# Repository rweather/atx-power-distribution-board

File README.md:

ATX Power Distribution Board
============================

This repository contains a design for an adapter board that connects
to a standard 24-pin ATX power supply connector and makes the
voltage rails available for homebrew computer use.

The board is designed to be retrofitted into an ITX computer case,
with the ITX power button, power LED, hdd LED, and reset button
connected to the board to provide power on/off control.

* [Schematic](schematics/ATX-Power-Distribution-Board/PDF/ATX-Power-Distribution-Board.pdf)

## License

Distributed under the terms of the MIT license.

## Contact

For more information on this code, to report bugs, or to suggest
improvements, please contact the author Rhys Weatherley via
[email](mailto:rhys.weatherley@gmail.com).

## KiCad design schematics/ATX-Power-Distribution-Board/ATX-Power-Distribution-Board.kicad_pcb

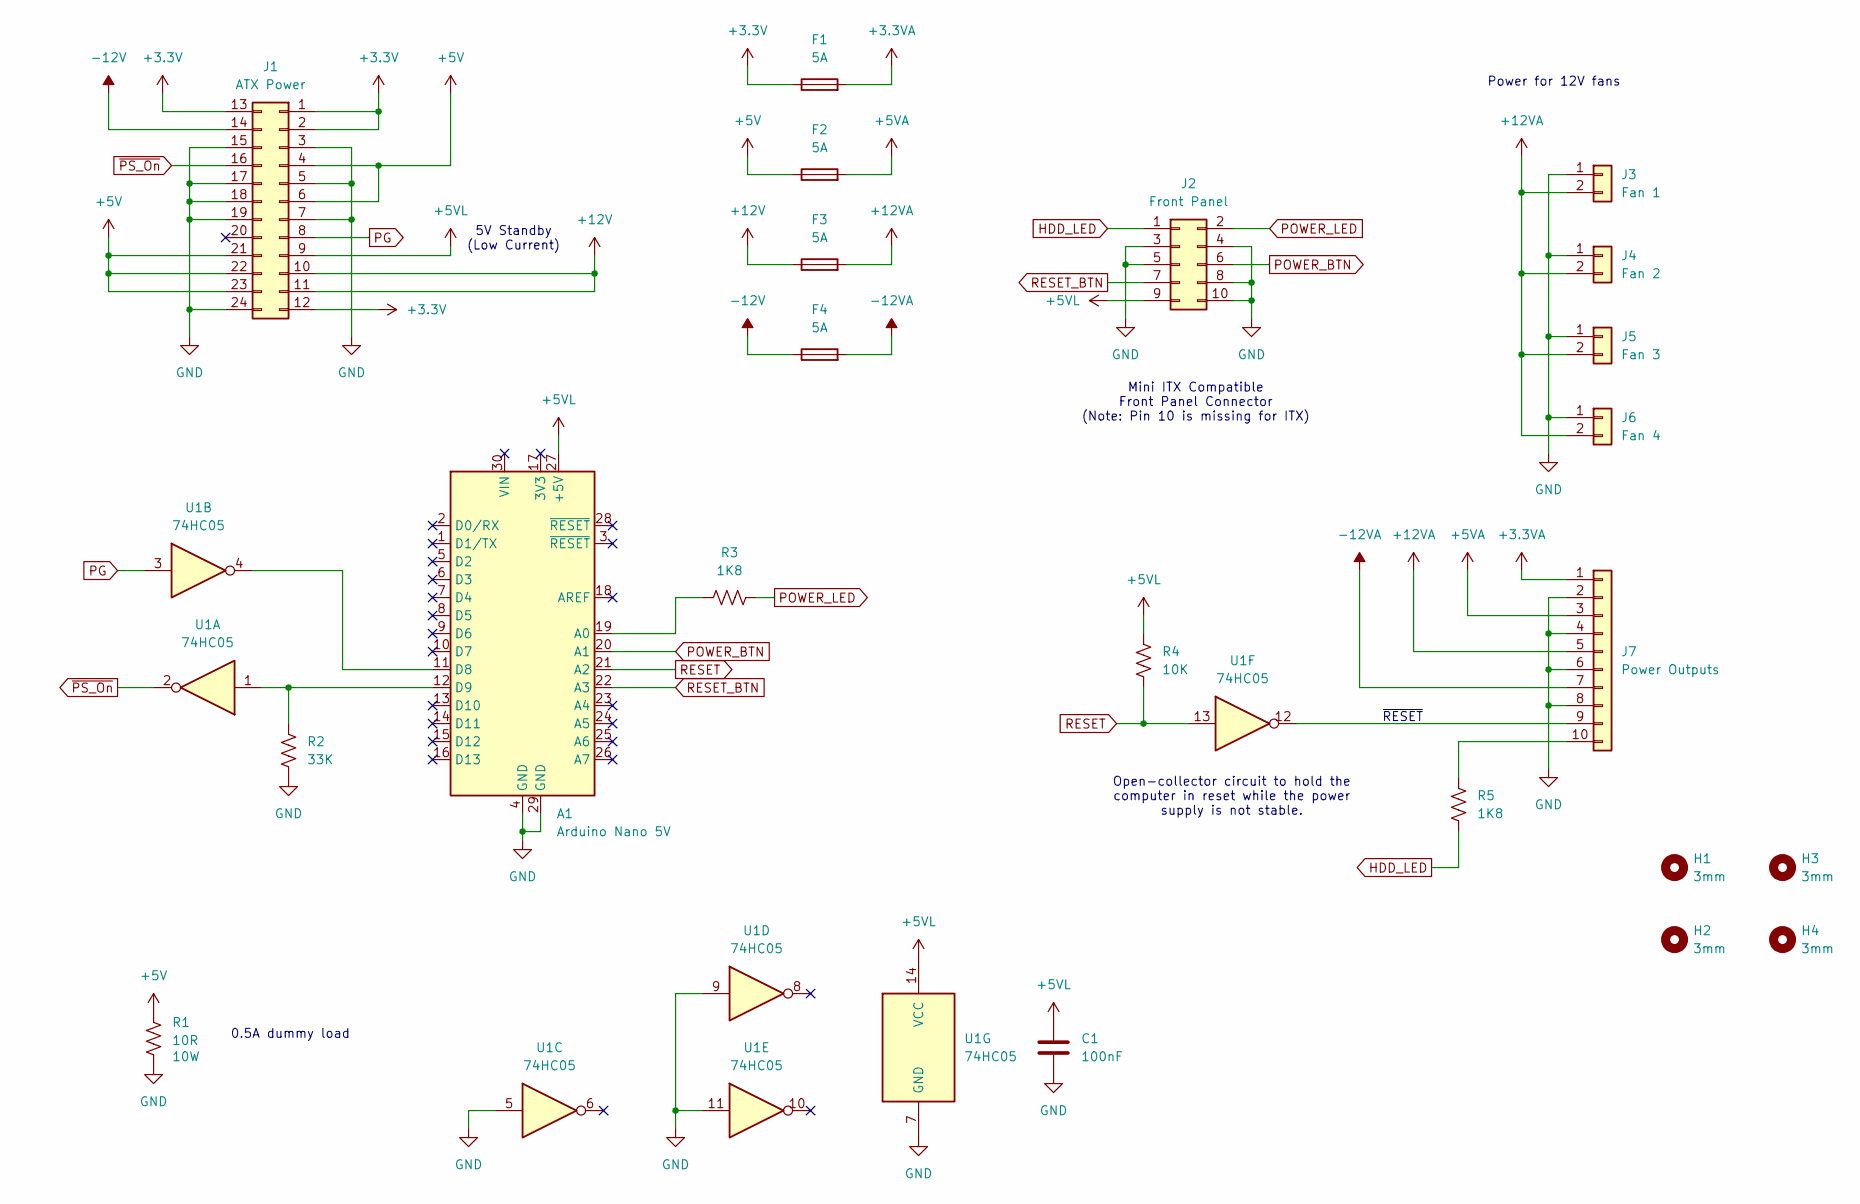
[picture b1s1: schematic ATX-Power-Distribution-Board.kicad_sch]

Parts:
A1: Arduino Nano 5V; Arduino_Nano
C1: 100nF; C_Disc_D5.0mm_W2.5mm_P5.00mm
F1, F2, F3, F4: 5A; Fuseholder_Clip-5x20mm_Littelfuse_111_Inline_P20.00x5.00mm_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
H1, H2, H3, H4: 3mm; MountingHole_3mm
J1: ATX Power; Molex_Mini-Fit_Jr_5569-24A2_2x12_P4.20mm_Horizontal
J2: Front Panel; PinHeader_2x05_P2.54mm_Vertical
J3: Fan 1; PinHeader_1x02_P2.54mm_Vertical
J4: Fan 2; PinHeader_1x02_P2.54mm_Vertical
J5: Fan 3; PinHeader_1x02_P2.54mm_Vertical
J6: Fan 4; PinHeader_1x02_P2.54mm_Vertical
J7: Power Outputs; PhoenixContact_MC_1,5_10-G-5.08_1x10_P5.08mm_Horizontal
R1: 10R; R_Axial_Power_L50.0mm_W9.0mm_P55.88mm; Rating 10W
R2: 33K; R_Axial_DIN0207_L6.3mm_D2.5mm_P10.16mm_Horizontal
R3, R5: 1K8; R_Axial_DIN0207_L6.3mm_D2.5mm_P10.16mm_Horizontal
R4: 10K; R_Axial_DIN0207_L6.3mm_D2.5mm_P10.16mm_Horizontal
U1: 74HC05; DIP-14_W7.62mm

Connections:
+3.3V: F1.1, J1.1, J1.2, J1.12, J1.13
+3.3VA: F1.2, J7.1
+5V: F2.1, J1.4, J1.6, J1.21, J1.22, J1.23, R1.1
+5VA: F2.2, J7.3
+5VL: A1.27 (+5V), C1.1, J1.9, J2.9, R4.1, U1.14 (VCC)
+12V: F3.1, J1.10, J1.11
+12VA: F3.2, J3.2, J4.2, J5.2, J6.2, J7.5
-12V: F4.1, J1.14
-12VA: F4.2, J7.7
GND: A1.4 (GND), A1.29 (GND), C1.2, J1.3, J1.5, J1.7, J1.15, J1.17, J1.18, J1.19, J1.24, J2.3, J2.4, J2.5, J2.8, J2.10, J3.1, J4.1, J5.1, J6.1, J7.2, J7.4, J7.6, J7.8, R1.2, R2.2, U1.5, U1.7 (GND), U1.9, U1.11
HDD_LED: J2.1, R5.2
unnamed: A1.19 (A0), R3.1
unnamed: A1.11 (D8), U1.4
unnamed: A1.12 (D9), R2.1, U1.1
unnamed: J7.9, U1.12
unnamed: J7.10, R5.1
PG: J1.8, U1.3
POWER_BTN: A1.20 (A1), J2.6
POWER_LED: J2.2, R3.2
RESET: A1.21 (A2), R4.2, U1.13
RESET_BTN: A1.22 (A3), J2.7
~PS_On: J1.16, U1.2

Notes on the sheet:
Mini ITX Compatible Front Panel Connector (Note: Pin 10 is missing for ITX)
Power for 12V fans
0.5A dummy load
~{RESET}
5V Standby (Low Current)
Open-collector circuit to hold the computer in reset while the power supply is not stable.

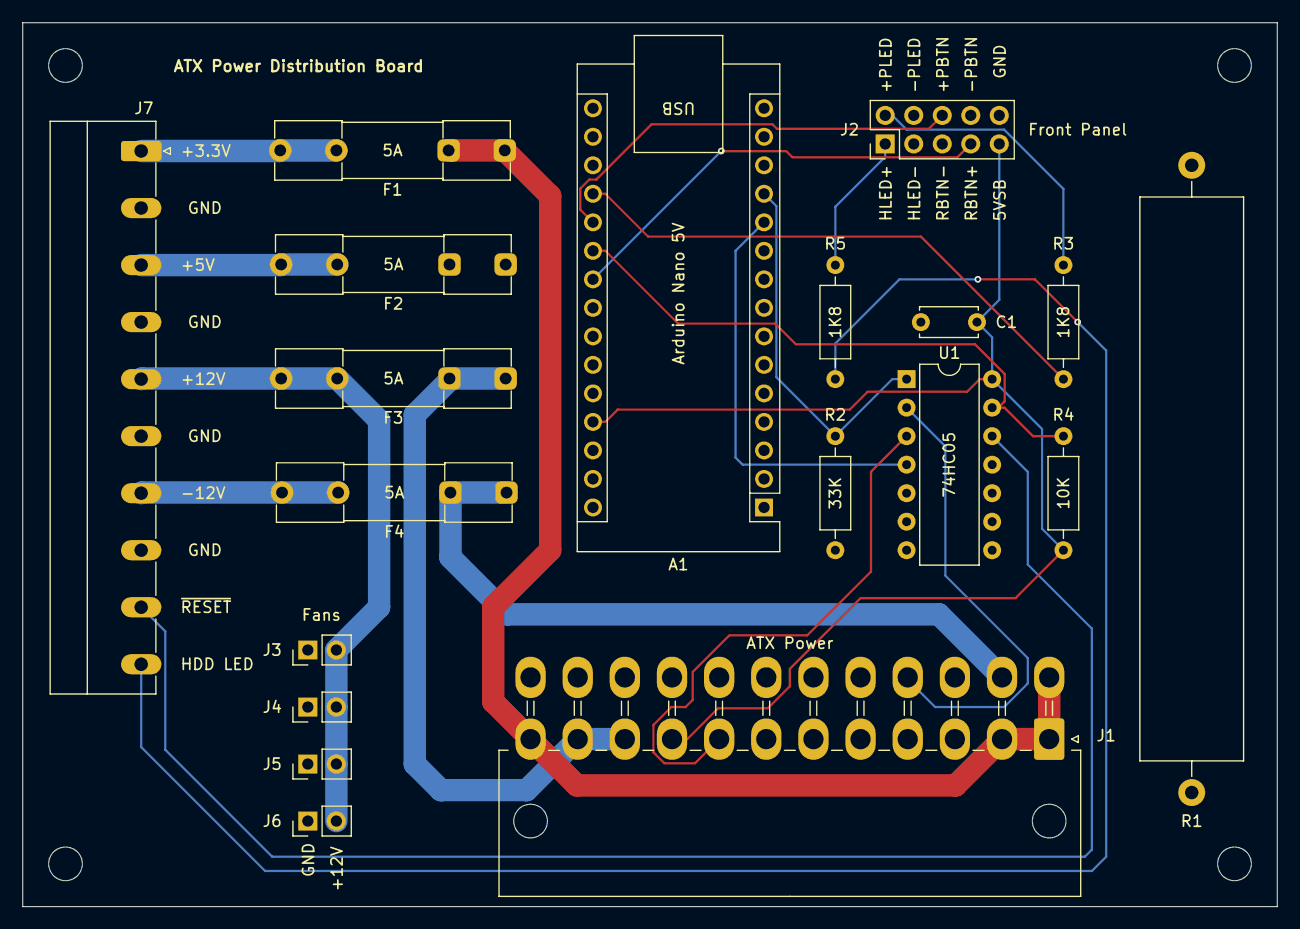
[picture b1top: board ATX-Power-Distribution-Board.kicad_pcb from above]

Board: 4 copper layers, 111.8 x 78.7 mm, 23 parts (0 on the bottom side), 22 nets.

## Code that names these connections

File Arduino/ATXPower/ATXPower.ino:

/*
 * Copyright (C) 2026 Rhys Weatherley
 *
 * Permission is hereby granted, free of charge, to any person obtaining a
 * copy of this software and associated documentation files (the "Software"),
 * to deal in the Software without restriction, including without limitation
 * the rights to use, copy, modify, merge, publish, distribute, sublicense,
 * and/or sell copies of the Software, and to permit persons to whom the
 * Software is furnished to do so, subject to the following conditions:
 *
 * The above copyright notice and this permission notice shall be included
 * in all copies or substantial portions of the Software.
 *
 * THE SOFTWARE IS PROVIDED "AS IS", WITHOUT WARRANTY OF ANY KIND, EXPRESS
 * OR IMPLIED, INCLUDING BUT NOT LIMITED TO THE WARRANTIES OF MERCHANTABILITY,
 * FITNESS FOR A PARTICULAR PURPOSE AND NONINFRINGEMENT. IN NO EVENT SHALL THE
 * AUTHORS OR COPYRIGHT HOLDERS BE LIABLE FOR ANY CLAIM, DAMAGES OR OTHER
 * LIABILITY, WHETHER IN AN ACTION OF CONTRACT, TORT OR OTHERWISE, ARISING
 * FROM, OUT OF OR IN CONNECTION WITH THE SOFTWARE OR THE USE OR OTHER
 * DEALINGS IN THE SOFTWARE.
 */

// Pin assignment.
#define STATUS_LED  13      // Status LED on the Arduino.
#define POWER_LED   A0      // Output, active-high, turn on the power LED.
#define POWER_BTN   A1      // Input, active-low, power button.
#define RESET_CTRL  A2      // Output, active-high, hold computer in reset.
#define RESET_BTN   A3      // Input, active-low, reset button.
#define POWER_GOOD  8       // Input, active-low, power supply is good.
#define POWER_ON    9       // Output, active-high, turn on power supply.

// Debounce timeouts for the power button, in milliseconds.
#define POWER_BTN_ON_TIME   100     // Press for 100ms to turn the system on.
#define POWER_BTN_OFF_TIME  1000    // Hold for 1s to turn the system off.

// Minimum time to hold the computer in reset when reset button pressed.
#define RESET_TIME          500

// Time to wait for the power good signal to go high before concluding
// that the power supply is not working correctly.
#define POWER_UP_TIME       5000

// States for the state machine.
typedef enum
{
    STATE_OFF,          // Computer is turned off.
    STATE_WAIT_ON,      // Power button pressed to turn on, wait for release.
    STATE_POWERING_UP,  // Power supply is turning on, computer held in reset.
    STATE_NORMAL,       // Computer is running normally.
    STATE_WAIT_OFF,     // Power button pressed to turn off, wait for release.
    STATE_WAIT_OFF2,    // Second stage power off, wait to lower reset line.
    STATE_WAIT_RESET,   // Reset button is pressed, wait for release.
    STATE_RESET         // Reset the computer due to the reset button.

} State_t;

State_t state = STATE_OFF;

class ButtonDebouncer
{
public:
    ButtonDebouncer(int pin);

    void run();
    bool isPressed() const { return pressed; }
    void setTimeout(unsigned long ms) { timeout = ms; }

private:
    int pinnum;
    bool rawPressed;
    bool pressed;
    bool timerRunning;
    unsigned long timer;
    unsigned long timeout;
};

ButtonDebouncer::ButtonDebouncer(int pin)
    : pinnum(pin)
    , rawPressed(false)
    , pressed(false)
    , timerRunning(false)
    , timer(0)
    , timeout(50)
{
}

void ButtonDebouncer::run()
{
    bool nowPressed = (digitalRead(pinnum) == LOW);
    if (nowPressed != rawPressed) {
        // Change in the raw state of the button.  Restart the timer.
        timer = millis();
        timerRunning = true;
        rawPressed = nowPressed;
    } else if (timerRunning) {
        if ((millis() - timer) >= timeout) {
            // Debounce time has elapsed.  Update the pressed state.
            pressed = nowPressed;
            timerRunning = false;
        }
    }
}

ButtonDebouncer powerButton(POWER_BTN);
ButtonDebouncer resetButton(RESET_BTN);
ButtonDebouncer powerGood(POWER_GOOD);

void setup()
{
    // Initialise the outputs.
    digitalWrite(POWER_LED, LOW);   // Power LED is off at startup.
    digitalWrite(STATUS_LED, LOW);
    digitalWrite(RESET_CTRL, HIGH); // Hold the computer in reset for now.
    digitalWrite(POWER_ON, LOW);    // Don't turn on the power supply yet.

    // Configure all pins to the desired modes.
    pinMode(STATUS_LED, OUTPUT);
    pinMode(POWER_LED, OUTPUT);
    pinMode(POWER_BTN, INPUT_PULLUP);
    pinMode(RESET_CTRL, OUTPUT);
    pinMode(RESET_BTN, INPUT_PULLUP);
    pinMode(POWER_GOOD, INPUT_PULLUP);
    pinMode(POWER_ON, OUTPUT);

    // Currently in the off state, waiting for the power button to be pressed.
    state = STATE_OFF;
    powerButton.setTimeout(POWER_BTN_ON_TIME);
}

// Shut down the computer immediately.
void shutdown(bool withReset = true)
{
    if (withReset) {
        digitalWrite(RESET_CTRL, HIGH);
    }
    digitalWrite(POWER_ON, LOW);
    digitalWrite(POWER_LED, LOW);
    digitalWrite(STATUS_LED, LOW);
    powerButton.setTimeout(POWER_BTN_ON_TIME);
}

static unsigned long global_timer = 0;
static unsigned long global_timeout = 0;

void startTimeout(unsigned long ms)
{
    global_timer = millis();
    global_timeout = ms;
}

bool isTimedOut()
{
    return (millis() - global_timer) >= global_timeout;
}

void loop()
{
    // Debounce the current state of the inputs.
    powerButton.run();
    resetButton.run();
    powerGood.run();

    // Run the state machine.
    switch (state) {
    case STATE_OFF:
        // Wait for the user to press the power button.
        if (powerButton.isPressed()) {
            state = STATE_WAIT_ON;
        }
        break;

    case STATE_WAIT_ON:
        // Wait for the user to release the power button.
        if (!powerButton.isPressed()) {
            // Turn on the supply, while still holding the computer in reset.
            digitalWrite(POWER_ON, HIGH);
            digitalWrite(POWER_LED, HIGH);
            digitalWrite(STATUS_LED, HIGH);
            powerButton.setTimeout(POWER_BTN_OFF_TIME);
            startTimeout(POWER_UP_TIME);
            state = STATE_POWERING_UP;
        }
        break;

    case STATE_POWERING_UP:
        // Power supply is on, waiting for the power good signal.
        if (powerGood.isPressed()) {
            // Hold the computer in reset for a little longer.
            startTimeout(RESET_TIME);
            state = STATE_RESET;
        } else if (isTimedOut()) {
            // Took too long for power good to come up.  Something went wrong.
            shutdown();
            state = STATE_OFF;
        }
        break;

    case STATE_NORMAL:
        // Normal operations.
        if (powerButton.isPressed()) {
            // User turned the power off.  Shut everything down except reset.
            shutdown(false);
            powerButton.setTimeout(POWER_BTN_ON_TIME);
            state = STATE_WAIT_OFF;
        } else if (resetButton.isPressed()) {
            // Explicit request to reset the attached computer.
            digitalWrite(RESET_CTRL, HIGH);
            state = STATE_WAIT_RESET;
        } else if (!powerGood.isPressed()) {
            // Power good signal from the power supply has gone away.
            // Shut the computer down immediately.
            shutdown();
            state = STATE_OFF;
        }
        break;

    case STATE_WAIT_OFF:
        // Wait for the power button to be released in the off state.
        if (!powerButton.isPressed()) {
            state = STATE_WAIT_OFF2;
            startTimeout(RESET_TIME);
        }
        break;

    case STATE_WAIT_OFF2:
        // After the timeout, forcibly reset the computer and stop.
        // It should have already lost power by now.
        if (isTimedOut()) {
            digitalWrite(RESET_CTRL, HIGH);
            state = STATE_OFF;
        }
        break;

    case STATE_WAIT_RESET:
        // Wait for the reset button to be released.
        if (!resetButton.isPressed()) {
            // Hold the computer in reset for a little longer after release.
            startTimeout(RESET_TIME);
            state = STATE_RESET;
        }
        break;

    case STATE_RESET:
        // Time to release the computer from reset?
        if (isTimedOut()) {
            digitalWrite(RESET_CTRL, LOW);
            state = STATE_NORMAL;
        }
        break;
    }
}

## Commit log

2026-01-30 Schematic for ATX power distribution board
2026-02-07 Arduino sketch to control the power supply
2026-02-07 License
2026-02-14 Update PDF schematic
2026-02-14 README
2026-02-14 Control the power LED from the Arduino sketch
